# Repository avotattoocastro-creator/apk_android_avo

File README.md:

# Evidencia visual iPad

Run 43643730930 · commit 9bfbfbfeb89852a982fcc8ad26d380f5716beb66 · rama feature/avo-equine-2-0

Capturas del simulador iPad Pro 13 pulgadas (M4) con sesiones de DEMOSTRACIÓN sintéticas.

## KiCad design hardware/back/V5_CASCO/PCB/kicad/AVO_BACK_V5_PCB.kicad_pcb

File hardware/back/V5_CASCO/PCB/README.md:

# AVO BACK V5 CASCO · PCB REV A (14/11/2026)

**Estado:** diseño verificado por software (KiCad 9 en el CI: DRC 0, 0 conexiones incompletas, paridad esquema ↔ placa 0, ERC 0/0). La puerta de fabricación está superada y los ficheros están en `out/FINAL/`. **No fabricada. No verificada en hardware.**

## Placa
- 51 × 51 mm, esquinas R3, 4 capas, 1,6 mm, ENIG.
- 4 taladros de Ø2,8 para los tornillos M2,5 de la caja, en (±22, ±22), y un paso de Ø3 para el coaxial de la antena.
- **Todos los componentes en la cara F**, que mira a la batería; la altura máxima es 2,6 mm.
- **B.Cu es masa maciza, sin pistas:** sirve de plano de masa de la antena GNSS plana activa de 25 × 25, pegada en el centro de la cara B.
- In1 es GND; In2 lleva señales y un relleno de +3V3.

## Bloques
- **ESP32-S3-MINI-1U-N8:** BLE con el móvil y ESP-NOW con el pecho y las cinchas. Antena FPC de 2,4 GHz en el conector del módulo, pegada a la pared de la cápsula.
- **ZED-F9P soldado.**
  - Comunicación con el S3: UART1 + UART2 + PPS + RESET.
  - 3,3 V propio con EN (RT9080).
  - V_BCKP desde el 3,3 V principal, para arrancar en caliente.
- **Antena activa:**
  - VCC_RF → 22 Ω en 1206 → 47 nH → línea de RF, protegida contra descargas;
  - línea de 50 Ω de 0,36 mm hasta RF_IN, con un puente de 0 Ω.
- **Pogo magnético de 5 contactos (por hilos):** VBUS, D−, D+, GND y AUX.
  - Protecciones: PTC y TVS en VBUS, USBLC6 en D±.
  - El USB nativo del S3 sirve para cargar, descargar sesiones y programar.
- **Cargador y alimentación:** cargador BQ24072, con unos 590 mA de carga y unos 800 mA de entrada; batería soldada con PTC; 3,3 V TLV75733P de 1 A.
- **microSD** con alimentación conmutada.
- **Hall DRV5032:** detecta el imán de la base del casco y despierta la placa.
- **Anillo de luz:** 8 LED RGB direccionables de emisión lateral **SK6812SIDE-A** (LCSC C5378721), 2 por lado (a ±12 mm del centro; ±10 abajo), con la lente a 0,3 mm del canto frente al anillo de resina.
  - Van en cadena desde el GPIO47 con 33 Ω en serie y se alimentan de VSYS.
  - La hoja pide 3,7–5,5 V: con la batería por debajo de unos 3,6 V pueden fallar.
  - Con los 8 en blanco al máximo consumen unos 290 mA; el firmware limita el brillo.

## Conexiones del ESP32-S3
| GPIO | Función | GPIO | Función |
|---|---|---|---|
| 1 | HALL (despertar) | 12–17 | microSD (SDMMC 4 bits) |
| 2 | BAT_ADC | 18 | VBUS_DET (despertar) |
| 4 | PPS del ZED | 19/20 | USB D−/D+ (pogo) |
| 5/6 | UART1 del ZED (RX/TX) | 21 | alimentación de la microSD (0 = encendida) |
| 7/8 | UART2 del ZED (RX/TX) | 38/39 | PGOOD / CHG del cargador |
| 9 | RESET_N del ZED | 40 | POGO_AUX |
| 10 | ZED_EN | 47 | datos del anillo de luz (8 × SK6812SIDE-A) |

## Pendiente antes de pedir
- Piezas sin código LCSC: ZED-F9P (suministrarlo aparte o por *global sourcing*), U.FL, bobina de 47 nH, 22 Ω en 1206 y ESD de RF.
- Modelo real del pogo de 5 contactos y de la batería (≥ 2000 mAh).
- Confirmar el ancho de la línea de 50 Ω con la calculadora de JLC.
- **Firmware:** poner GPIO6, GPIO8 y GPIO9 como entradas antes de bajar ZED_EN.
- **Prueba de la antena** sobre un plano de 51 × 51: tiempo hasta el fix y ruido de velocidad.

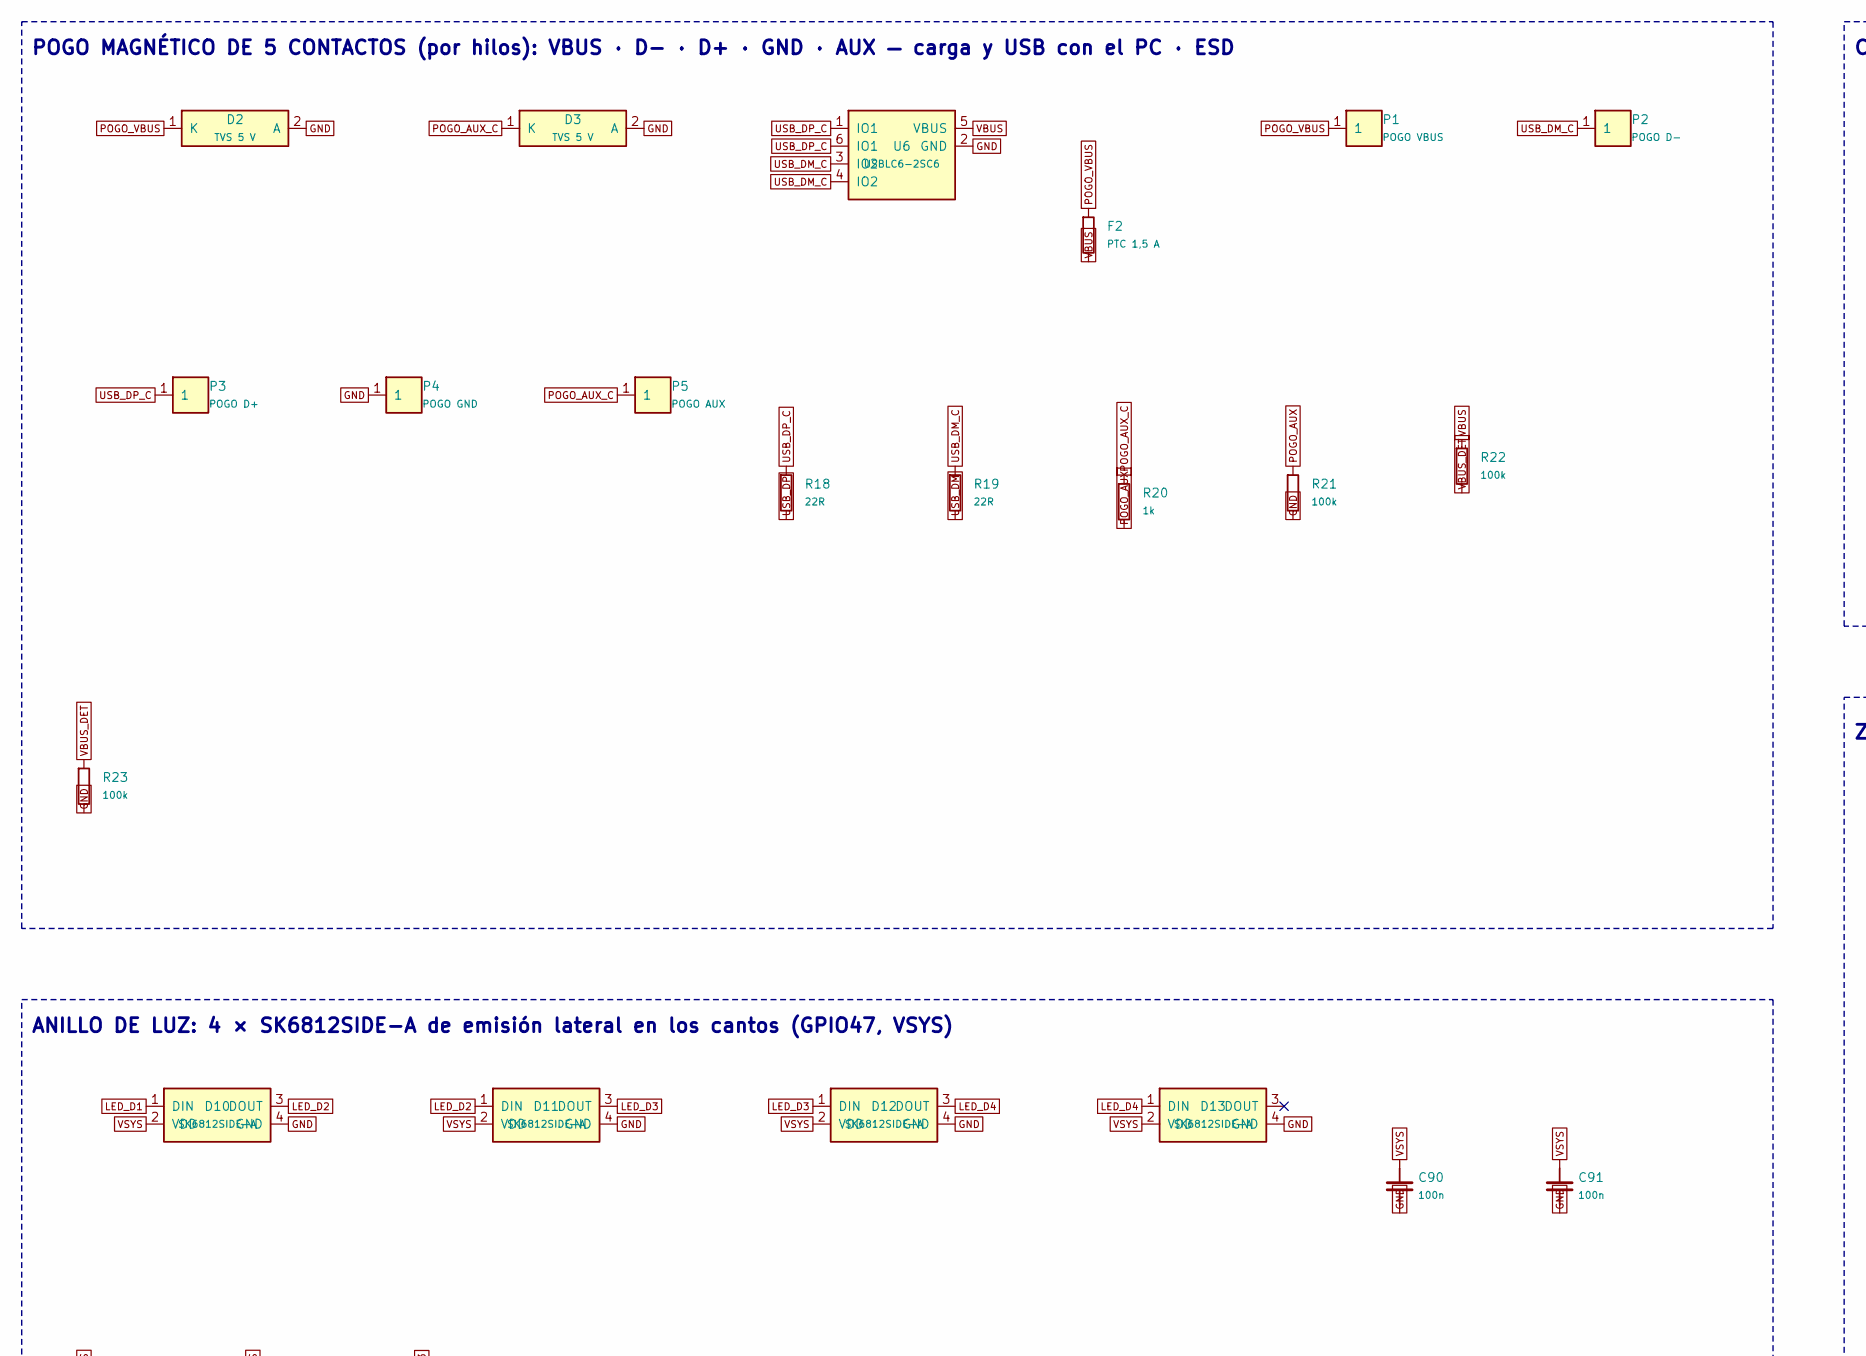
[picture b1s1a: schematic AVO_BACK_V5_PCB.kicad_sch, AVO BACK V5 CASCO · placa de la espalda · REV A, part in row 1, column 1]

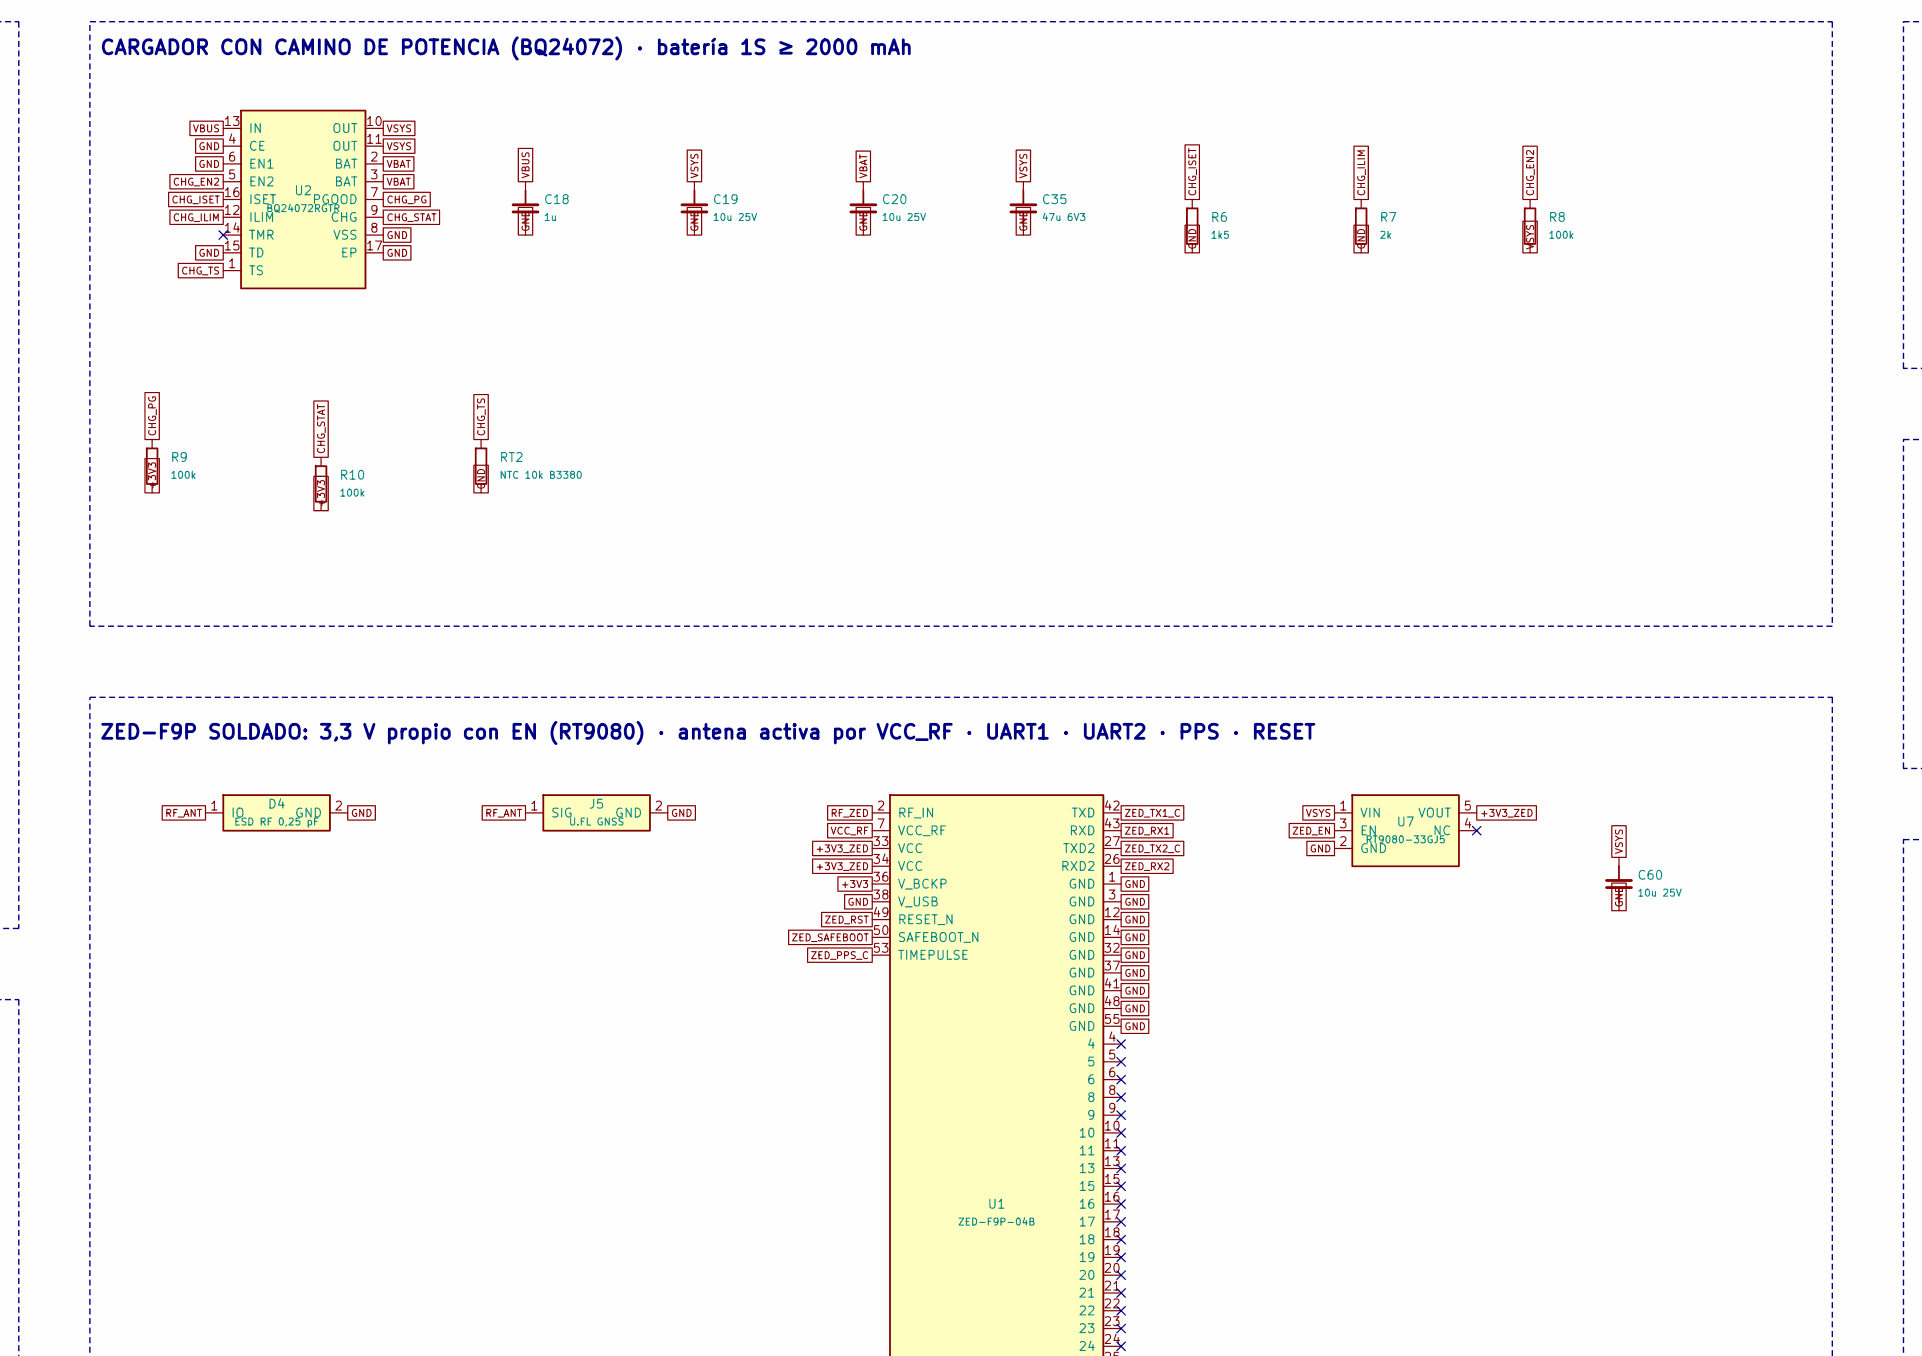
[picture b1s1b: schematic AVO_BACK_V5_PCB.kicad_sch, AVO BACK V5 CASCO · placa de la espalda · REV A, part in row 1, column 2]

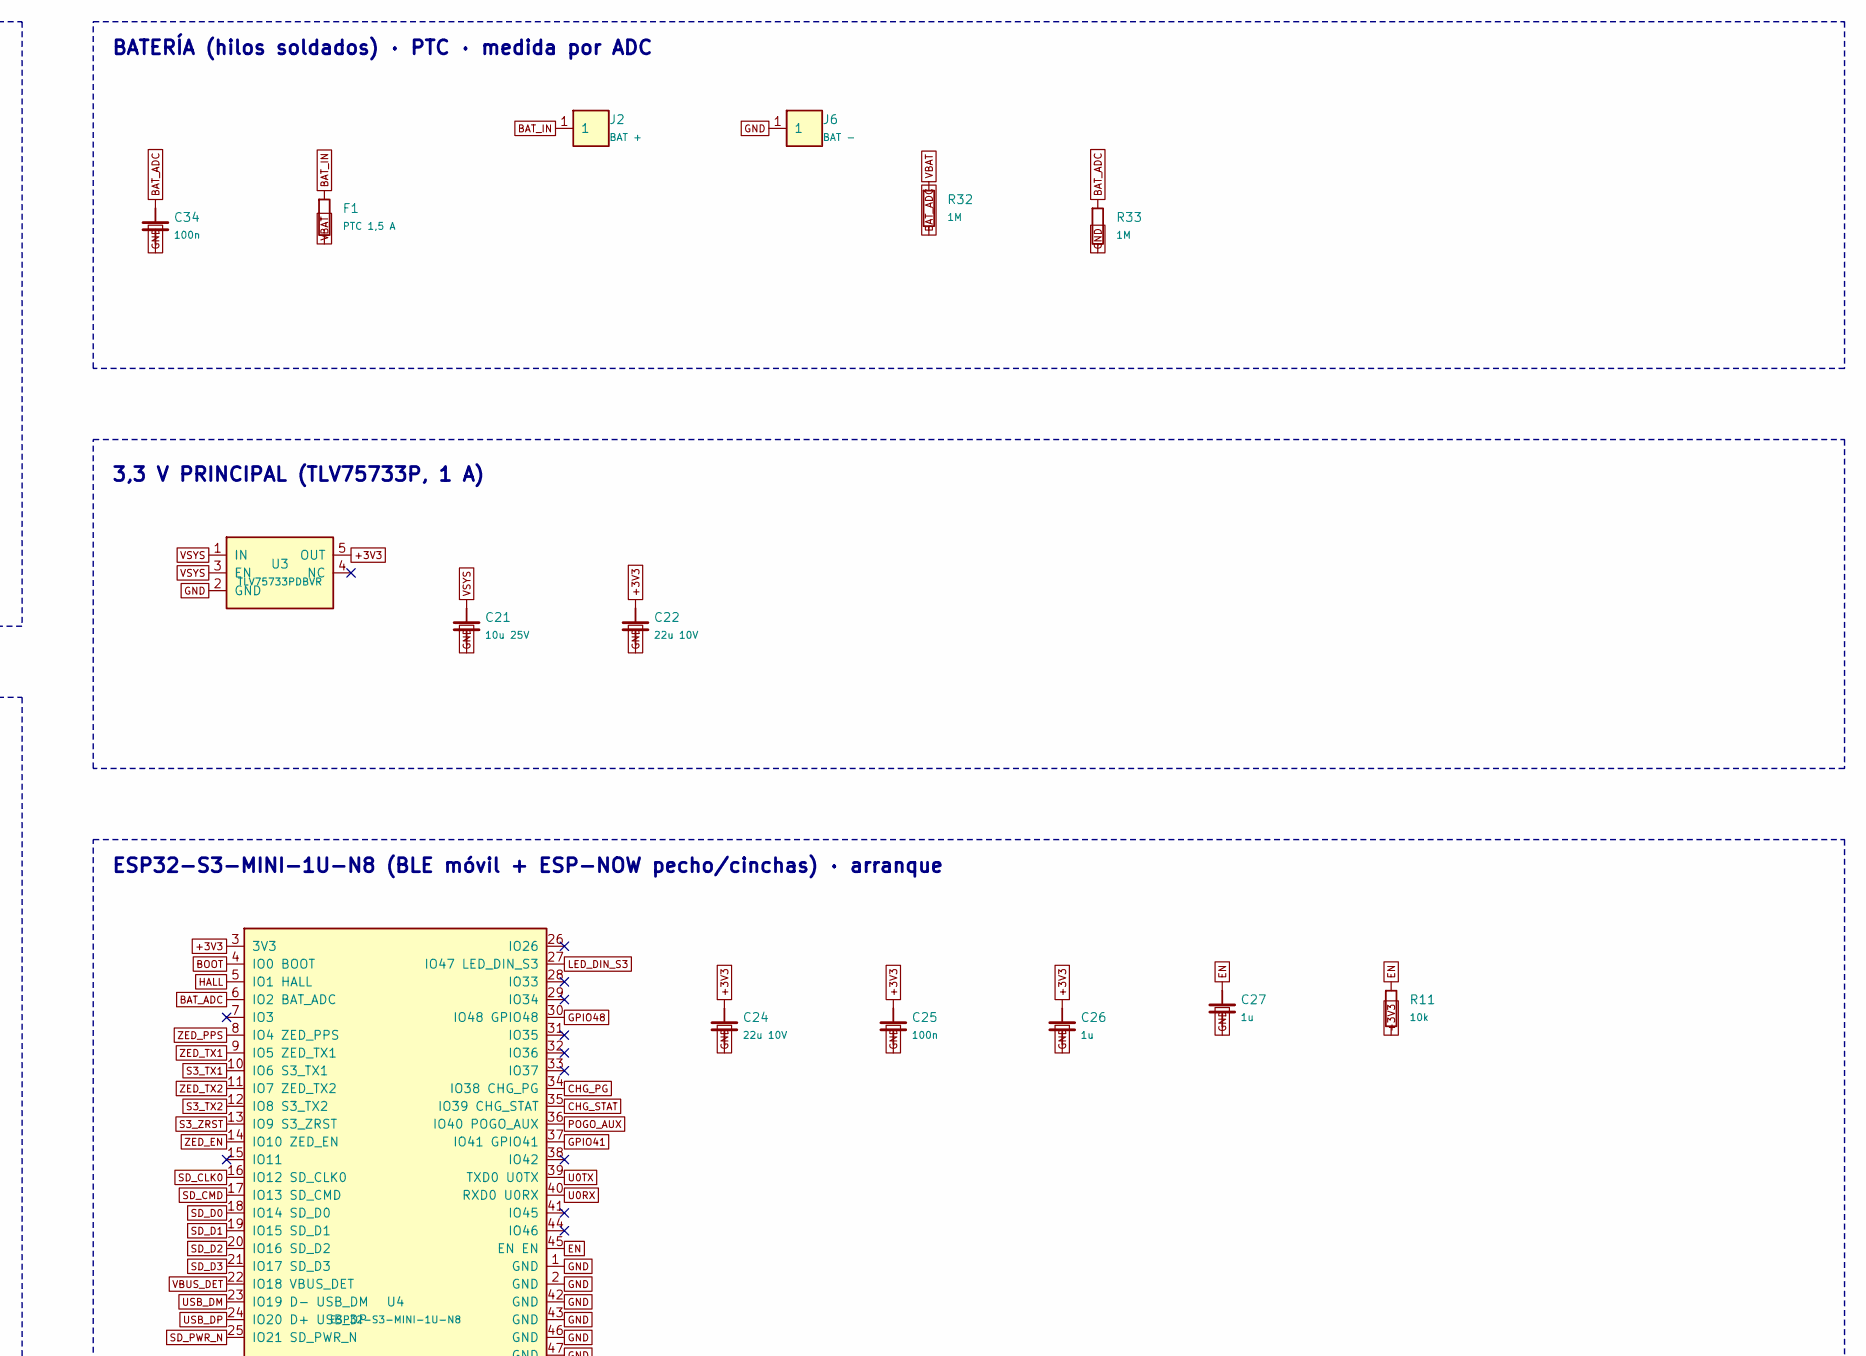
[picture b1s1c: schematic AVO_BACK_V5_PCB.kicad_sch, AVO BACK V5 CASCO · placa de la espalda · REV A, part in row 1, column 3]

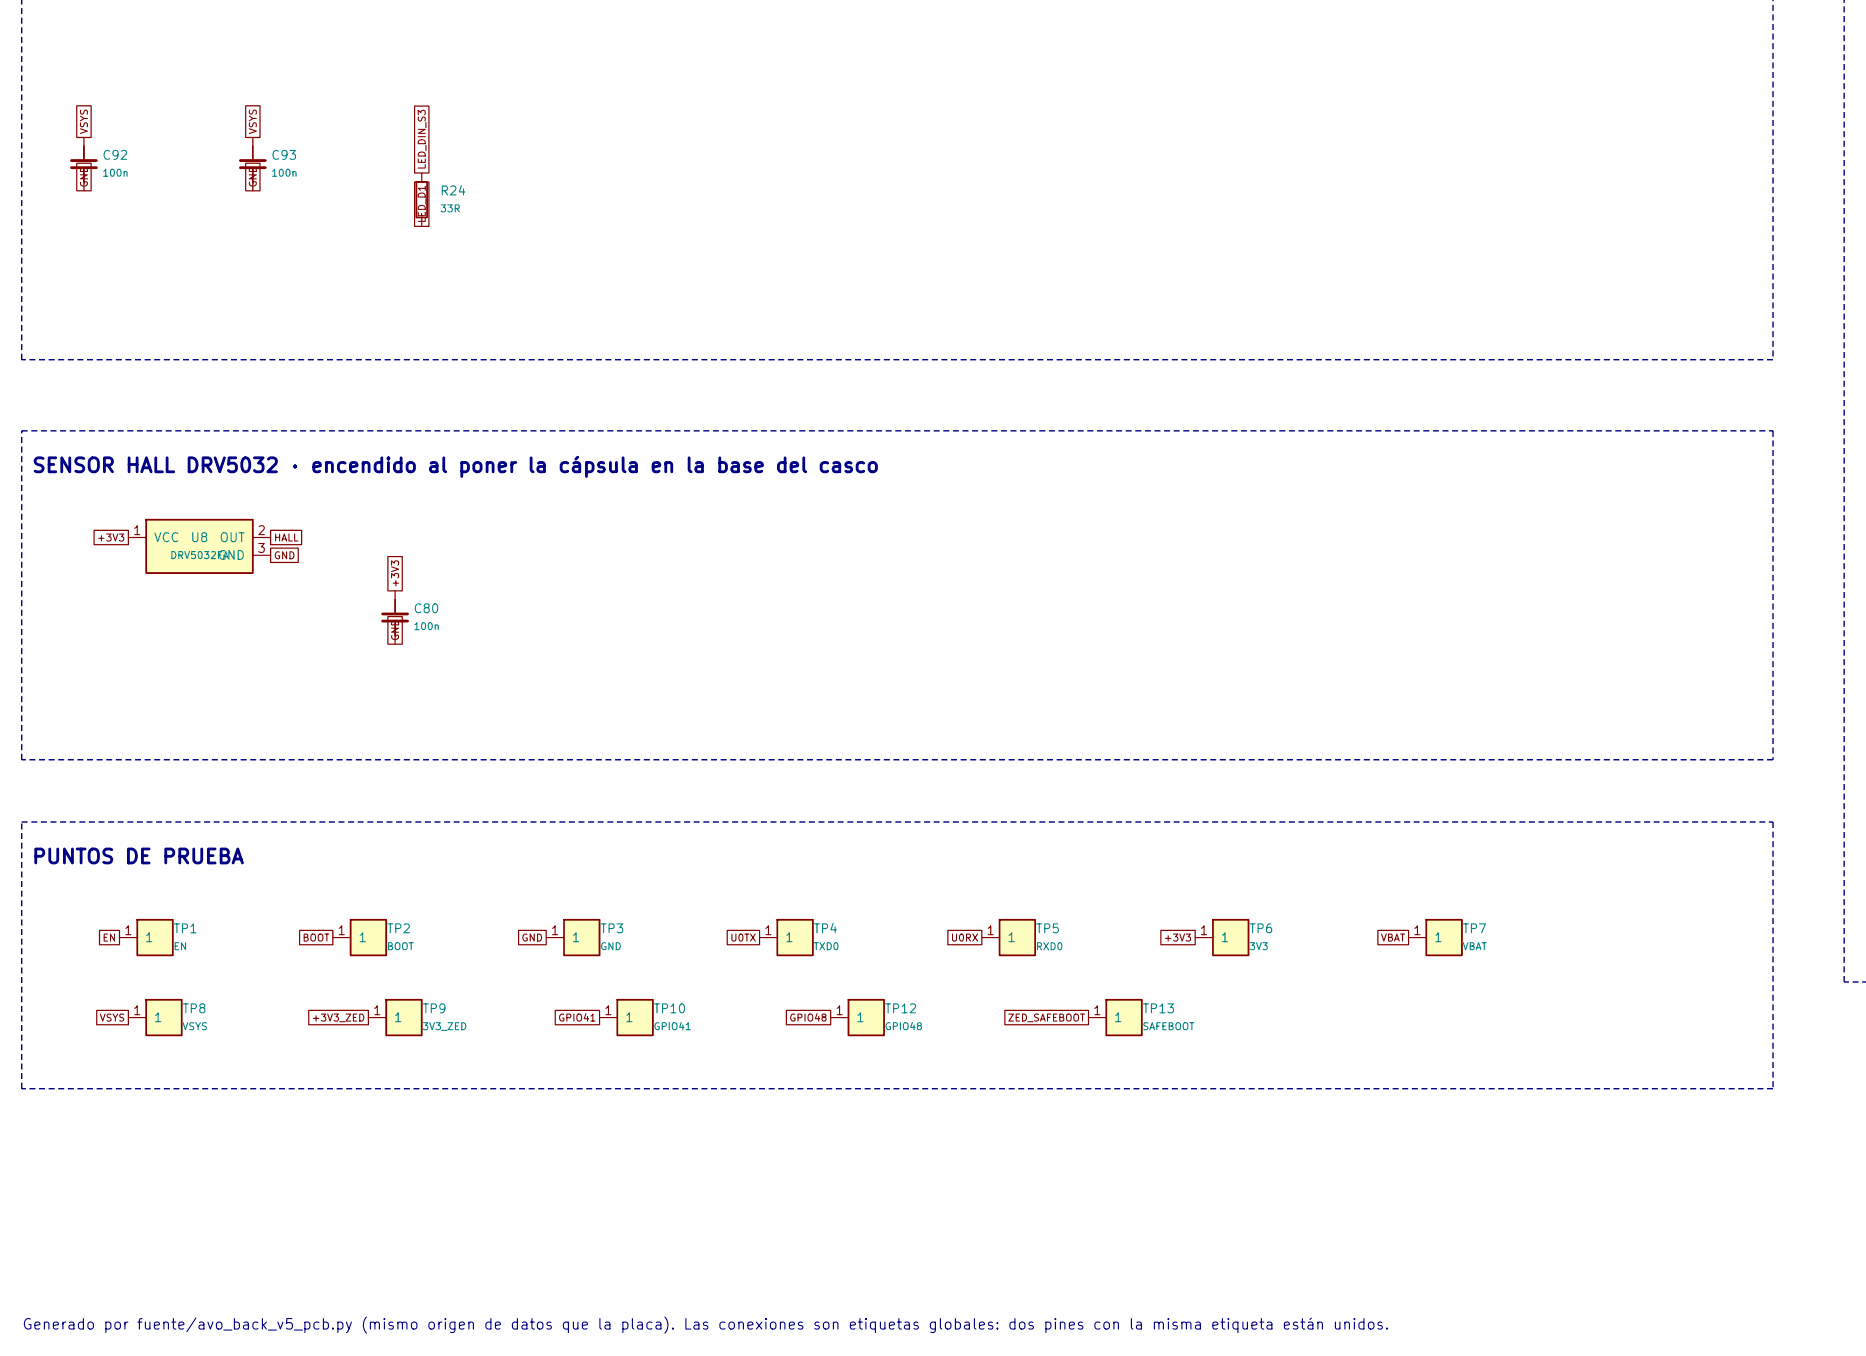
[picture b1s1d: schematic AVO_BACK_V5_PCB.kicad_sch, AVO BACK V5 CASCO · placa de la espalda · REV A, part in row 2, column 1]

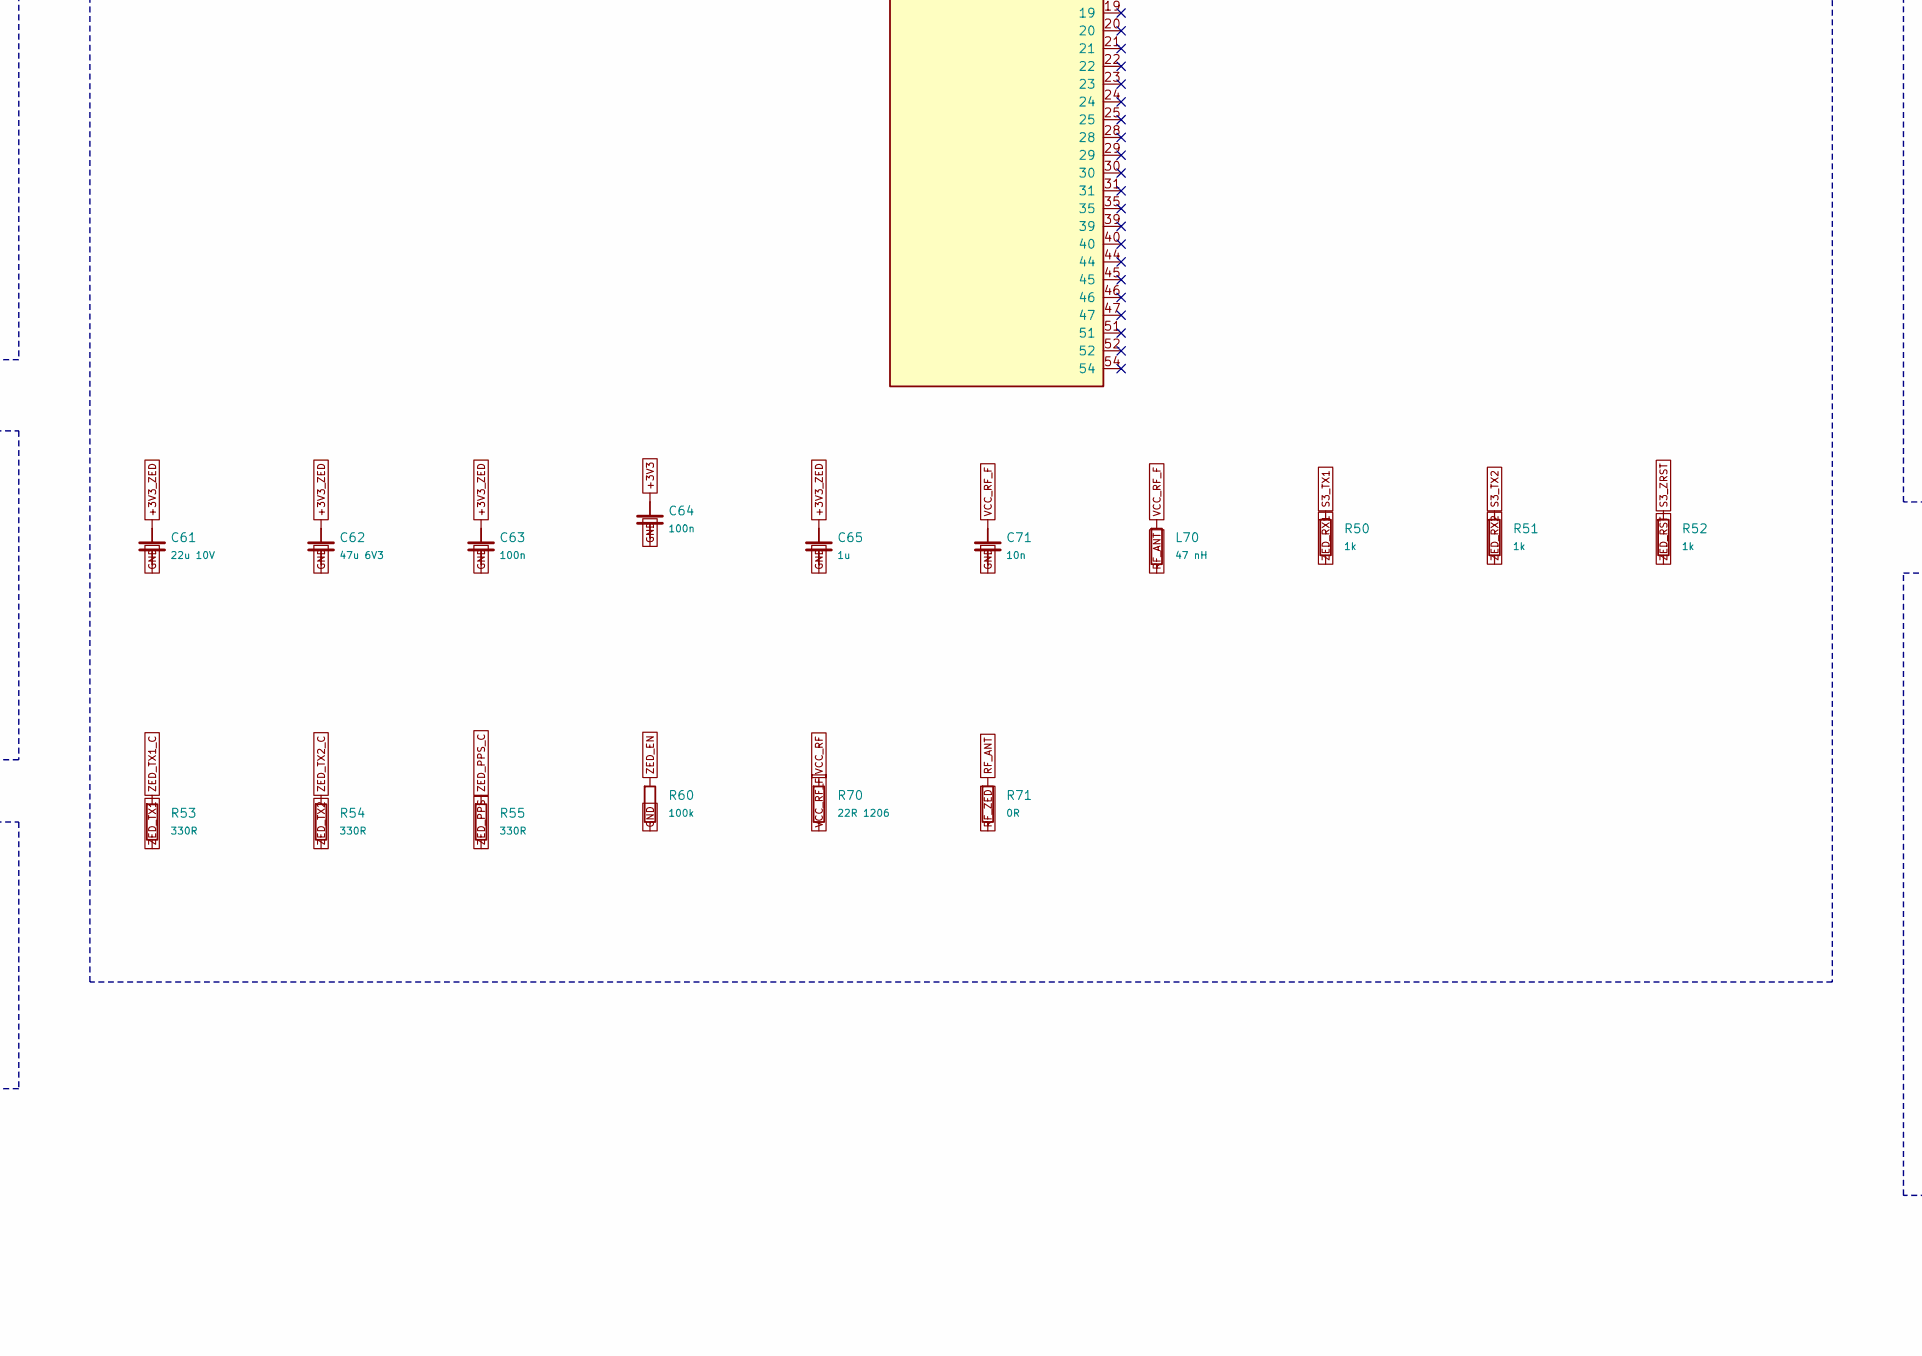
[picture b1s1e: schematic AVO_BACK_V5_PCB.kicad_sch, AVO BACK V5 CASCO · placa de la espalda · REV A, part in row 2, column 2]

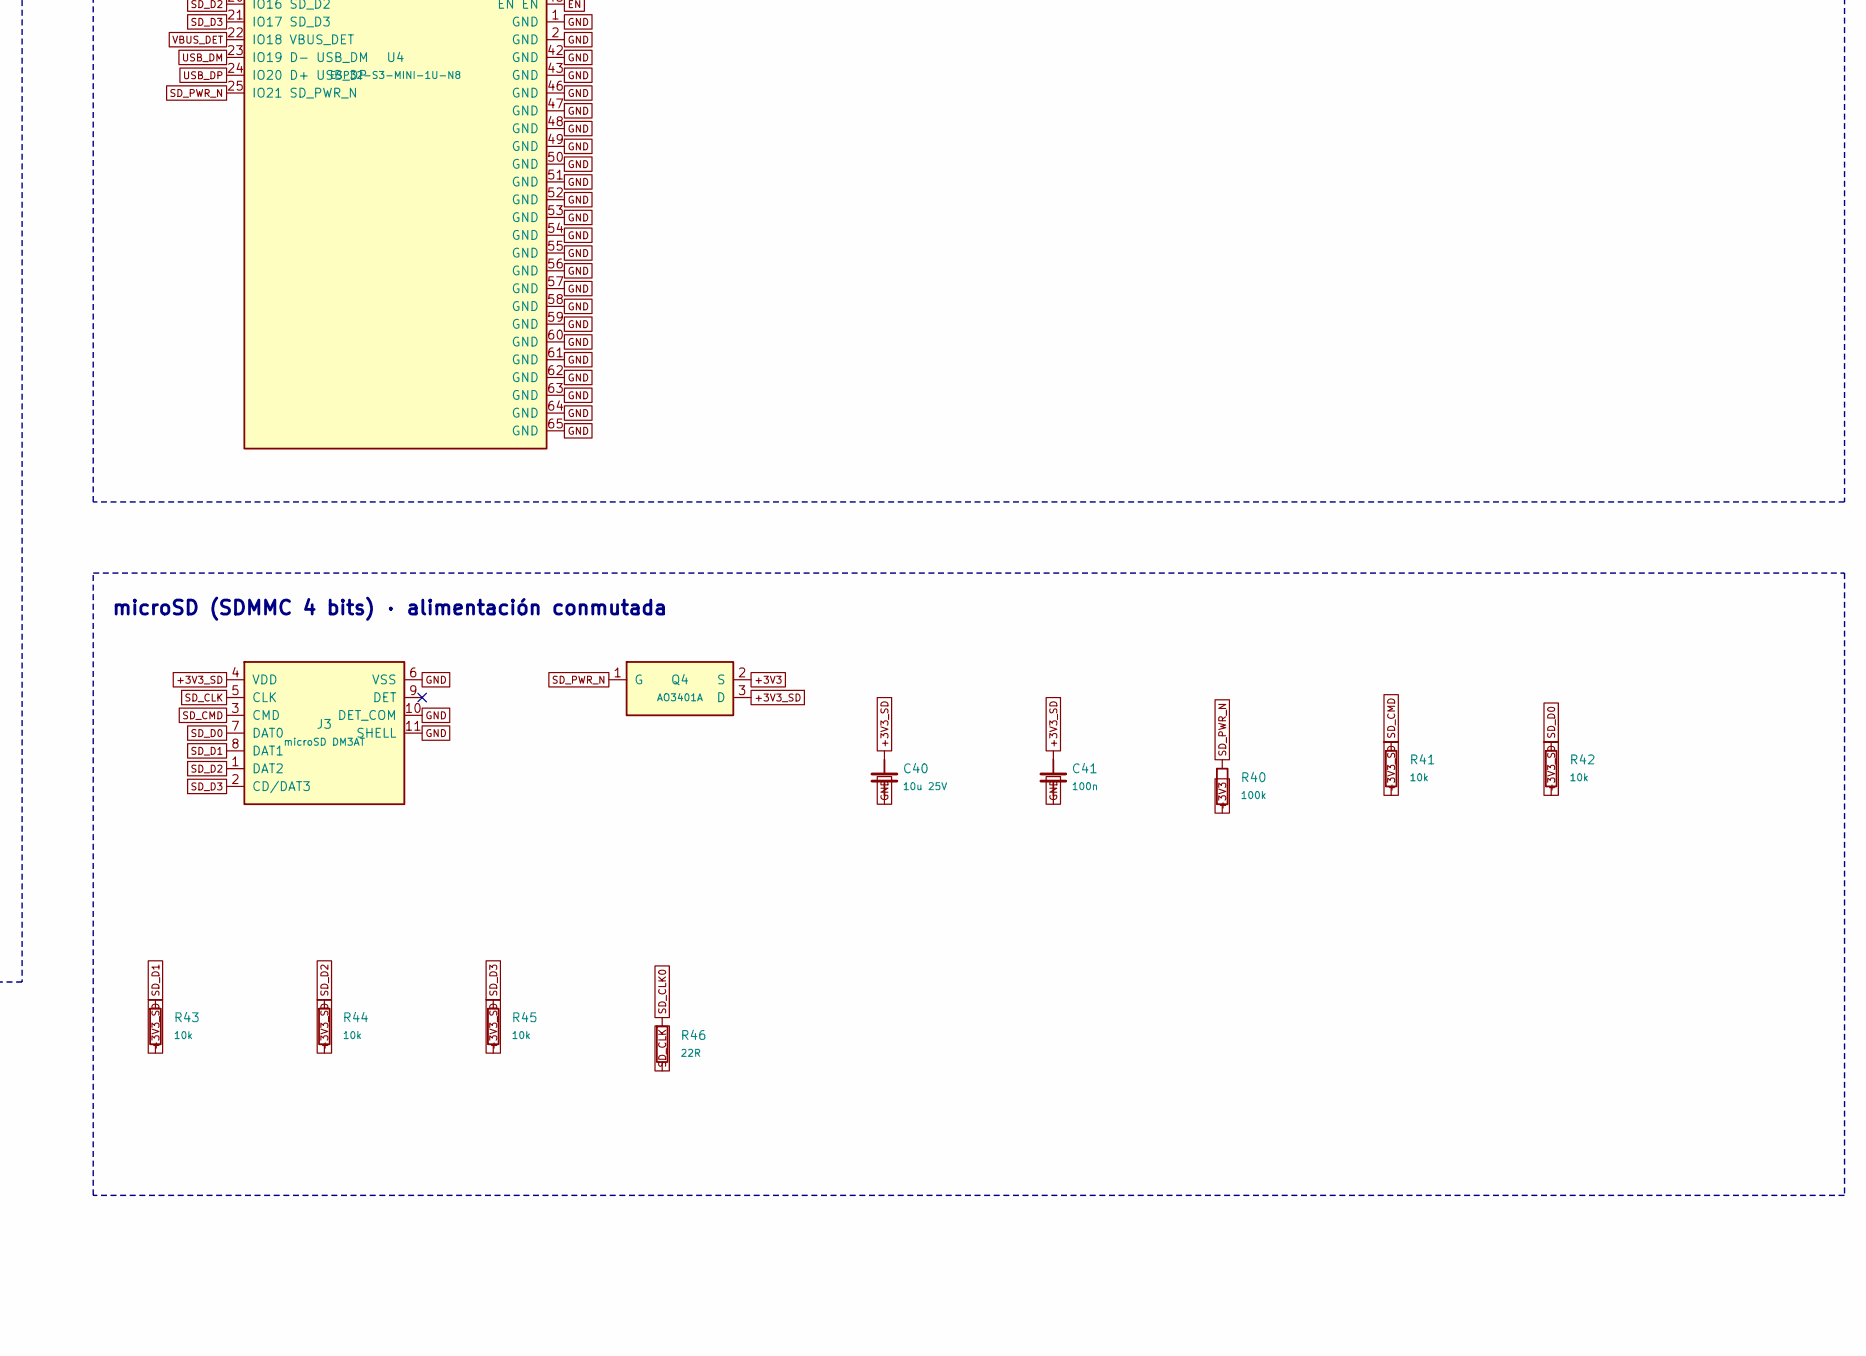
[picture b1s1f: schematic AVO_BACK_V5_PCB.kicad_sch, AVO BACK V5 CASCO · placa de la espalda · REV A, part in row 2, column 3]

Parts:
C18, C26, C27, C65: 1u; C_0402_1005Metric; LCSC C52923
C19, C20, C21, C40, C60: 10u 25V; C_0603_1608Metric; LCSC C96446
C22, C24, C61: 22u 10V; C_0805_2012Metric; LCSC C45783
C25, C34, C41, C63, C64, C80, C90, C91, C92, C93: 100n; C_0402_1005Metric; LCSC C1525
C35, C62: 47u 6V3; C_0805_2012Metric; LCSC C16780
C71: 10n; C_0402_1005Metric; LCSC C15195
D2, D3: TVS 5 V; D_SOD-323; MPN PESD5V0S1BA; LCSC C2827694
D4: ESD RF 0,25 pF; C_0402_1005Metric; MPN PESD0402-140 (Littelfuse/TE); LCSC C10662
D10, D11, D12, D13: SK6812SIDE-A; AVO_SK6812SIDE-A_4.0x1.6mm; MPN SK6812SIDE-A (OPSCO); LCSC C5378721
F1, F2: PTC 1,5 A; Fuse_1206_3216Metric; MPN SMD1206P150TF; LCSC C20802
J2: BAT +; WirePad_D1.7_Drill0.9
J3: microSD DM3AT; microSD_HC_Hirose_DM3AT-SF-PEJM5; MPN DM3AT-SF-PEJM5; LCSC C114218
J5: U.FL GNSS; U.FL_Hirose_U.FL-R-SMT-1_Vertical; MPN U.FL-R-SMT-1(10) (Hirose); LCSC C88373
J6: BAT −; WirePad_D1.7_Drill0.9
L70: 47 nH; R_0402_1005Metric; MPN LQG15HS47NJ02D (Murata); LCSC C97998
P1: POGO VBUS; WirePad_D1.7_Drill0.9
P2: POGO D−; WirePad_D1.7_Drill0.9
P3: POGO D+; WirePad_D1.7_Drill0.9
P4: POGO GND; WirePad_D1.7_Drill0.9
P5: POGO AUX; WirePad_D1.7_Drill0.9
Q4: AO3401A; SOT-23; LCSC C15127
R6: 1k5; R_0402_1005Metric; LCSC C25867
R7: 2k; R_0402_1005Metric; LCSC C4109
R8, R9, R10, R21, R22, R23, R40, R60: 100k; R_0402_1005Metric; LCSC C25741
R11, R41, R42, R43, R44, R45: 10k; R_0402_1005Metric; LCSC C25744
R18, R19, R46: 22R; R_0402_1005Metric; LCSC C25092
R20, R50, R51, R52: 1k; R_0402_1005Metric; LCSC C11702
R24: 33R; R_0402_1005Metric; LCSC C25105
R32, R33: 1M; R_0402_1005Metric; LCSC C26083
R53, R54, R55: 330R; R_0402_1005Metric; LCSC C25104
R70: 22R 1206; C_1206_3216Metric; LCSC C17958
R71: 0R; R_0402_1005Metric; LCSC C17168
RT2: NTC 10k B3380; R_0402_1005Metric; MPN NCP15XH103F03RC; LCSC C77131
TP1: EN; TestPoint_Pad_D1.0mm
TP2: BOOT; TestPoint_Pad_D1.0mm
TP3: GND; TestPoint_Pad_D1.0mm
TP4: TXD0; TestPoint_Pad_D1.0mm
TP5: RXD0; TestPoint_Pad_D1.0mm
TP6: 3V3; TestPoint_Pad_D1.0mm
TP7: VBAT; TestPoint_Pad_D1.0mm
TP8: VSYS; TestPoint_Pad_D1.0mm
TP9: 3V3_ZED; TestPoint_Pad_D1.0mm
TP10: GPIO41; TestPoint_Pad_D1.0mm
TP12: GPIO48; TestPoint_Pad_D1.0mm
TP13: SAFEBOOT; TestPoint_Pad_D1.0mm
U1: ZED-F9P-04B; ublox_ZED; MPN ZED-F9P-04B (u-blox); LCSC C5120257
U2: BQ24072RGTR; VQFN-16-1EP_3x3mm_P0.5mm_EP1.68x1.68mm_ThermalVias; MPN BQ24072RGTR; LCSC C140288
U3: TLV75733PDBVR; SOT-23-5; MPN TLV75733PDBVR; LCSC C485517
U4: ESP32-S3-MINI-1U-N8; ESP32-S3-MINI-1U; MPN ESP32-S3-MINI-1U-N8; LCSC C2980299
U6: USBLC6-2SC6; SOT-23-6; LCSC C7519
U7: RT9080-33GJ5; SOT-23-5; MPN RT9080-33GJ5; LCSC C841192
U8: DRV5032FA; SOT-23; MPN DRV5032FADBZR; LCSC C140921

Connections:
+3V3: C22.1, C24.1, C25.1, C26.1, C64.1, C80.1, Q4.2 (S), R9.2, R10.2, R11.2, R40.2, TP6.1, U1.36 (V_BCKP), U3.5 (OUT), U4.3 (3V3), U8.1 (VCC)
+3V3_SD: C40.1, C41.1, J3.4 (VDD), Q4.3 (D), R41.2, R42.2, R43.2, R44.2, R45.2
+3V3_ZED: C61.1, C62.1, C63.1, C65.1, TP9.1, U1.33 (VCC), U1.34 (VCC), U7.5 (VOUT)
BAT_ADC: C34.1, R32.2, R33.1, U4.6 (IO2 BAT_ADC)
BAT_IN: F1.1, J2.1
BOOT: TP2.1, U4.4 (IO0 BOOT)
CHG_EN2: R8.1, U2.5 (EN2)
CHG_ILIM: R7.1, U2.12 (ILIM)
CHG_ISET: R6.1, U2.16 (ISET)
CHG_PG: R9.1, U2.7 (PGOOD), U4.34 (IO38 CHG_PG)
CHG_STAT: R10.1, U2.9 (CHG), U4.35 (IO39 CHG_STAT)
CHG_TS: RT2.1, U2.1 (TS)
EN: C27.1, R11.1, TP1.1, U4.45 (EN EN)
GND: C18.2, C19.2, C20.2, C21.2, C22.2, C24.2, C25.2, C26.2, C27.2, C34.2, C35.2, C40.2, C41.2, C60.2, C61.2, C62.2, C63.2, C64.2, C65.2, C71.2, C80.2, C90.2, C91.2, C92.2, C93.2, D2.2 (A), D3.2 (A), D4.2 (GND), D10.4 (GND), D11.4 (GND), D12.4 (GND), D13.4 (GND), J3.6 (VSS), J3.10 (DET_COM), J3.11 (SHELL), J5.2 (GND), J6.1, P4.1, R6.2, R7.2, R21.2, R23.2, R33.2, R60.2, RT2.2, TP3.1, U1.1 (GND), U1.3 (GND), U1.12 (GND), U1.14 (GND), U1.32 (GND), U1.37 (GND), U1.38 (V_USB), U1.41 (GND), U1.48 (GND), U1.55 (GND), U2.4 (CE), U2.6 (EN1), U2.8 (VSS), U2.15 (TD), U2.17 (EP), U3.2 (GND), U4.1 (GND), U4.2 (GND), U4.42 (GND), U4.43 (GND), U4.46 (GND), U4.47 (GND), U4.48 (GND), U4.49 (GND), U4.50 (GND), U4.51 (GND), U4.52 (GND), U4.53 (GND), U4.54 (GND), U4.55 (GND), U4.56 (GND), U4.57 (GND), U4.58 (GND), U4.59 (GND), U4.60 (GND), U4.61 (GND), U4.62 (GND), U4.63 (GND), U4.64 (GND), U4.65 (GND), U6.2 (GND), U7.2 (GND), U8.3 (GND); also elsewhere on the board
GPIO41: TP10.1, U4.37 (IO41 GPIO41)
GPIO48: TP12.1, U4.30 (IO48 GPIO48)
HALL: U4.5 (IO1 HALL), U8.2 (OUT)
LED_D1: D10.1 (DIN), R24.2
LED_D2: D10.3 (DOUT), D11.1 (DIN)
LED_D3: D11.3 (DOUT), D12.1 (DIN)
LED_D4: D12.3 (DOUT), D13.1 (DIN)
LED_D5: D13.3 (DOUT); also elsewhere on the board
LED_DIN_S3: R24.1, U4.27 (IO47 LED_DIN_S3)
POGO_AUX: R20.2, R21.1, U4.36 (IO40 POGO_AUX)
POGO_AUX_C: D3.1 (K), P5.1, R20.1
POGO_VBUS: D2.1 (K), F2.1, P1.1
RF_ANT: D4.1 (IO), J5.1 (SIG), L70.2, R71.1
RF_ZED: R71.2, U1.2 (RF_IN)
S3_TX1: R50.1, U4.10 (IO6 S3_TX1)
S3_TX2: R51.1, U4.12 (IO8 S3_TX2)
S3_ZRST: R52.1, U4.13 (IO9 S3_ZRST)
SD_CLK: J3.5 (CLK), R46.2
SD_CLK0: R46.1, U4.16 (IO12 SD_CLK0)
SD_CMD: J3.3 (CMD), R41.1, U4.17 (IO13 SD_CMD)
SD_D0: J3.7 (DAT0), R42.1, U4.18 (IO14 SD_D0)
SD_D1: J3.8 (DAT1), R43.1, U4.19 (IO15 SD_D1)
SD_D2: J3.1 (DAT2), R44.1, U4.20 (IO16 SD_D2)
SD_D3: J3.2 (CD/DAT3), R45.1, U4.21 (IO17 SD_D3)
SD_PWR_N: Q4.1 (G), R40.1, U4.25 (IO21 SD_PWR_N)
U0RX: TP5.1, U4.40 (RXD0 U0RX)
U0TX: TP4.1, U4.39 (TXD0 U0TX)
USB_DM: R19.2, U4.23 (IO19 D- USB_DM)
USB_DM_C: P2.1, R19.1, U6.3 (IO2), U6.4 (IO2)
USB_DP: R18.2, U4.24 (IO20 D+ USB_DP)
USB_DP_C: P3.1, R18.1, U6.1 (IO1), U6.6 (IO1)
VBAT: C20.1, F1.2, R32.1, TP7.1, U2.2 (BAT), U2.3 (BAT)
VBUS: C18.1, F2.2, R22.1, U2.13 (IN), U6.5 (VBUS)
VBUS_DET: R22.2, R23.1, U4.22 (IO18 VBUS_DET)
VCC_RF: R70.1, U1.7 (VCC_RF)
VCC_RF_F: C71.1, L70.1, R70.2
VSYS: C19.1, C21.1, C35.1, C60.1, C90.1, C91.1, C92.1, C93.1, D10.2 (VDD), D11.2 (VDD), D12.2 (VDD), D13.2 (VDD), R8.2, TP8.1, U2.10 (OUT), U2.11 (OUT), U3.1 (IN), U3.3 (EN), U7.1 (VIN); also elsewhere on the board
ZED_EN: R60.1, U4.14 (IO10 ZED_EN), U7.3 (EN)
ZED_PPS: R55.2, U4.8 (IO4 ZED_PPS)
ZED_PPS_C: R55.1, U1.53 (TIMEPULSE)
ZED_RST: R52.2, U1.49 (RESET_N)
ZED_RX1: R50.2, U1.43 (RXD)
ZED_RX2: R51.2, U1.26 (RXD2)
ZED_SAFEBOOT: TP13.1, U1.50 (SAFEBOOT_N)
ZED_TX1: R53.2, U4.9 (IO5 ZED_TX1)
ZED_TX1_C: R53.1, U1.42 (TXD)
ZED_TX2: R54.2, U4.11 (IO7 ZED_TX2)
ZED_TX2_C: R54.1, U1.27 (TXD2)

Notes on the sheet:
POGO MAGNÉTICO DE 5 CONTACTOS (por hilos): VBUS · D− · D+ · GND · AUX — carga y USB con el PC · ESD
ZED-F9P SOLDADO: 3,3 V propio con EN (RT9080) · antena activa por VCC_RF · UART1 · UART2 · PPS · RESET
ANILLO DE LUZ: 4 × SK6812SIDE-A de emisión lateral en los cantos (GPIO47, VSYS)
microSD (SDMMC 4 bits) · alimentación conmutada
CARGADOR CON CAMINO DE POTENCIA (BQ24072) · batería 1S ≥ 2000 mAh
3,3 V PRINCIPAL (TLV75733P, 1 A)
ESP32-S3-MINI-1U-N8 (BLE móvil + ESP-NOW pecho/cinchas) · arranque
SENSOR HALL DRV5032 · encendido al poner la cápsula en la base del casco
BATERÍA (hilos soldados) · PTC · medida por ADC
PUNTOS DE PRUEBA
Generado por fuente/avo_back_v5_pcb.py (mismo origen de datos que la placa). Las conexiones son etiquetas globales: dos pines con la misma etiqueta están unidos.

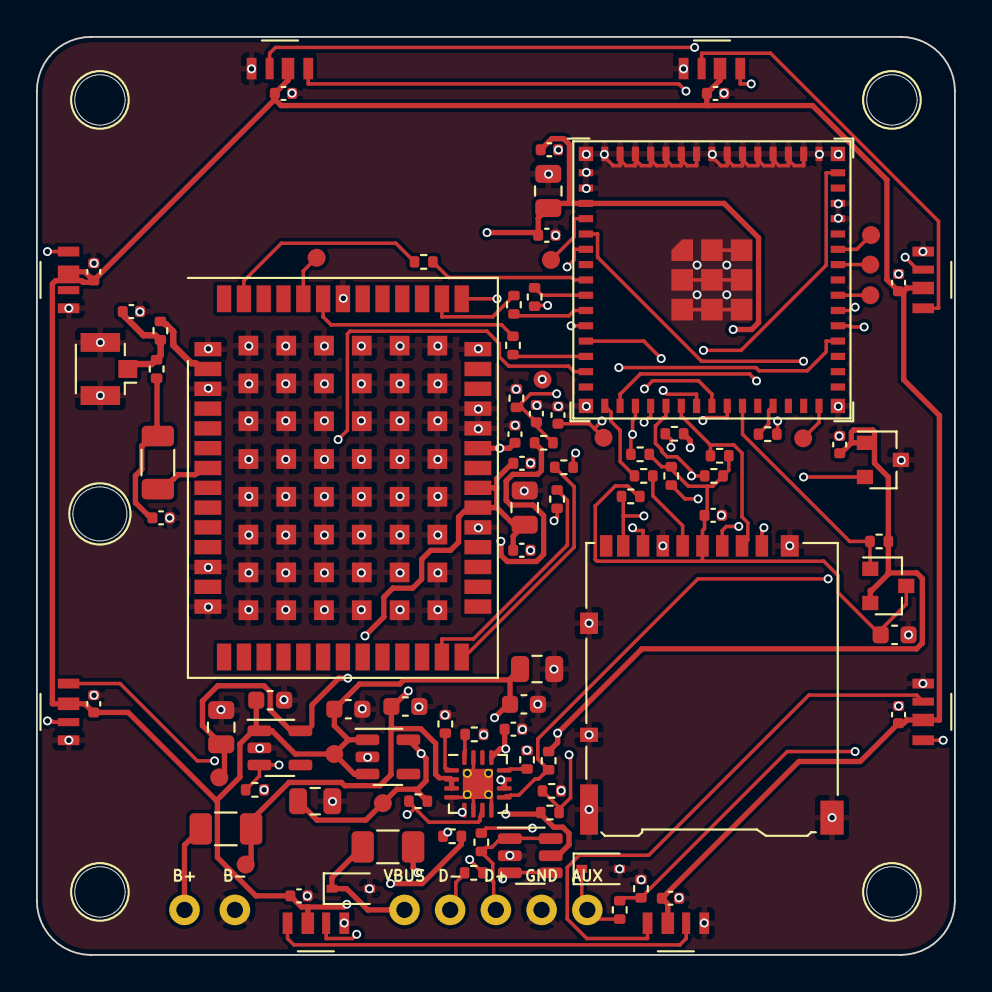
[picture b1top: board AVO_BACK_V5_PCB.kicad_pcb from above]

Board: 4 copper layers, 51.0 x 51.0 mm, 109 parts (0 on the bottom side), 65 nets.

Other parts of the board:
C94, C95, C96, C97: 100n; C_0402_1005Metric
D14, D15, D16, D17: SK6812SIDE-A; AVO_SK6812SIDE-A_4.0x1.6mm
H1, H2, H3, H4: TALADRO M2,5; AVO_Taladro_NPTH_D2.8
H5: PASO COAXIAL; AVO_Taladro_NPTH_D3.0

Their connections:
GND: C94.2, C95.2, C96.2, C97.2, D14.4, D15.4, D16.4, D17.4; also elsewhere on the board
LED_D5: D14.1; also elsewhere on the board
LED_D6: D14.3, D15.1
LED_D7: D15.3, D16.1
LED_D8: D16.3, D17.1
VSYS: C94.1, C95.1, C96.1, C97.1, D14.2, D15.2, D16.2, D17.2; also elsewhere on the board

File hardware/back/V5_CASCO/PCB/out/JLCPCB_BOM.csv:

Comment,Designator,Footprint,LCSC Part #
"PTC 1,5 A","F1,F2",Fuse_1206_3216Metric,C20802
TVS 5 V,"D2,D3",D_SOD-323,C2827694
1k,"R20,R50,R51,R52",R_0402_1005Metric,C11702
100k,"R8,R9,R10,R21,R22,R23,R40,R60",R_0402_1005Metric,C25741
USBLC6-2SC6,U6,SOT-23-6,C7519
22R,"R18,R19,R46",R_0402_1005Metric,C25092
BQ24072RGTR,U2,VQFN-16-1EP_3x3mm_P0.5mm_EP1.68x1.68mm_ThermalVias,C140288
1u,"C18,C26,C27,C65",C_0402_1005Metric,C52923
10u 25V,"C19,C20,C21,C40,C60",C_0603_1608Metric,C96446
47u 6V3,"C35,C62",C_0805_2012Metric,C16780
1k5,R6,R_0402_1005Metric,C25867
2k,R7,R_0402_1005Metric,C4109
NTC 10k B3380,RT2,R_0402_1005Metric,C77131
1M,"R32,R33",R_0402_1005Metric,C26083
100n,"C25,C34,C41,C63,C64,C80,C90,C91,C92,C93,C94,C95,C96,C97",C_0402_1005Metric,C1525
TLV75733PDBVR,U3,SOT-23-5,C485517
22u 10V,"C22,C24,C61",C_0805_2012Metric,C45783
RT9080-33GJ5,U7,SOT-23-5,C841192
ZED-F9P-04B,U1,ublox_ZED,C5120257
22R 1206,R70,C_1206_3216Metric,C17958
10n,C71,C_0402_1005Metric,C15195
47 nH,L70,R_0402_1005Metric,C97998
0R,R71,R_0402_1005Metric,C17168
"ESD RF 0,25 pF",D4,C_0402_1005Metric,C10662
U.FL GNSS,J5,U.FL_Hirose_U.FL-R-SMT-1_Vertical,C88373
330R,"R53,R54,R55",R_0402_1005Metric,C25104
ESP32-S3-MINI-1U-N8,U4,ESP32-S3-MINI-1U,C2980299
10k,"R11,R41,R42,R43,R44,R45",R_0402_1005Metric,C25744
33R,R24,R_0402_1005Metric,C25105
SK6812SIDE-A,"D10,D11,D12,D13,D14,D15,D16,D17",AVO_SK6812SIDE-A_4.0x1.6mm,C5378721
DRV5032FA,U8,SOT-23,C140921
microSD DM3AT,J3,microSD_HC_Hirose_DM3AT-SF-PEJM5,C114218
AO3401A,Q4,SOT-23,C15127
